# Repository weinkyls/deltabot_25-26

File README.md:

# The Delta Bot

### What is the Delta Bot?
The Delta Bot is an open-source DIY robot AI platform that uses Radxa's single board computer, the [Rock 5B](https://radxa.com/products/rock5/5b/), a simple [camera module](https://www.raspberrypi.com/products/camera-module-v2/), Parallax's [Continuous Rotation Servo Motors](https://www.parallax.com/product/parallax-continuous-rotation-servo-factory-centered/), and the [RPLIDAR A1](https://www.slamtec.com/en/lidar/a1), a LIDAR camera by Slamtec.

### Purpose & Vision

### What can it do?

- 360 Degree 2D LiDAR Scans
- Precise Servo Movement 
- 1080p Video Capture
- Can be configured for Line Following, SLAM, Obstacle Detection, and more!

### Additional Mechanical Parts
Additional Mechanical Parts were designed in CAD and can be accessed [here](additional_files/deltabot.f3z).
These were used to secure the external components onto the Single PCB Chassis:

## Credits
- Saleh AlMulla - 2721704A@student.gla.ac.uk
- Bernd Porr -  bernd.porr@glasgow.ac.uk

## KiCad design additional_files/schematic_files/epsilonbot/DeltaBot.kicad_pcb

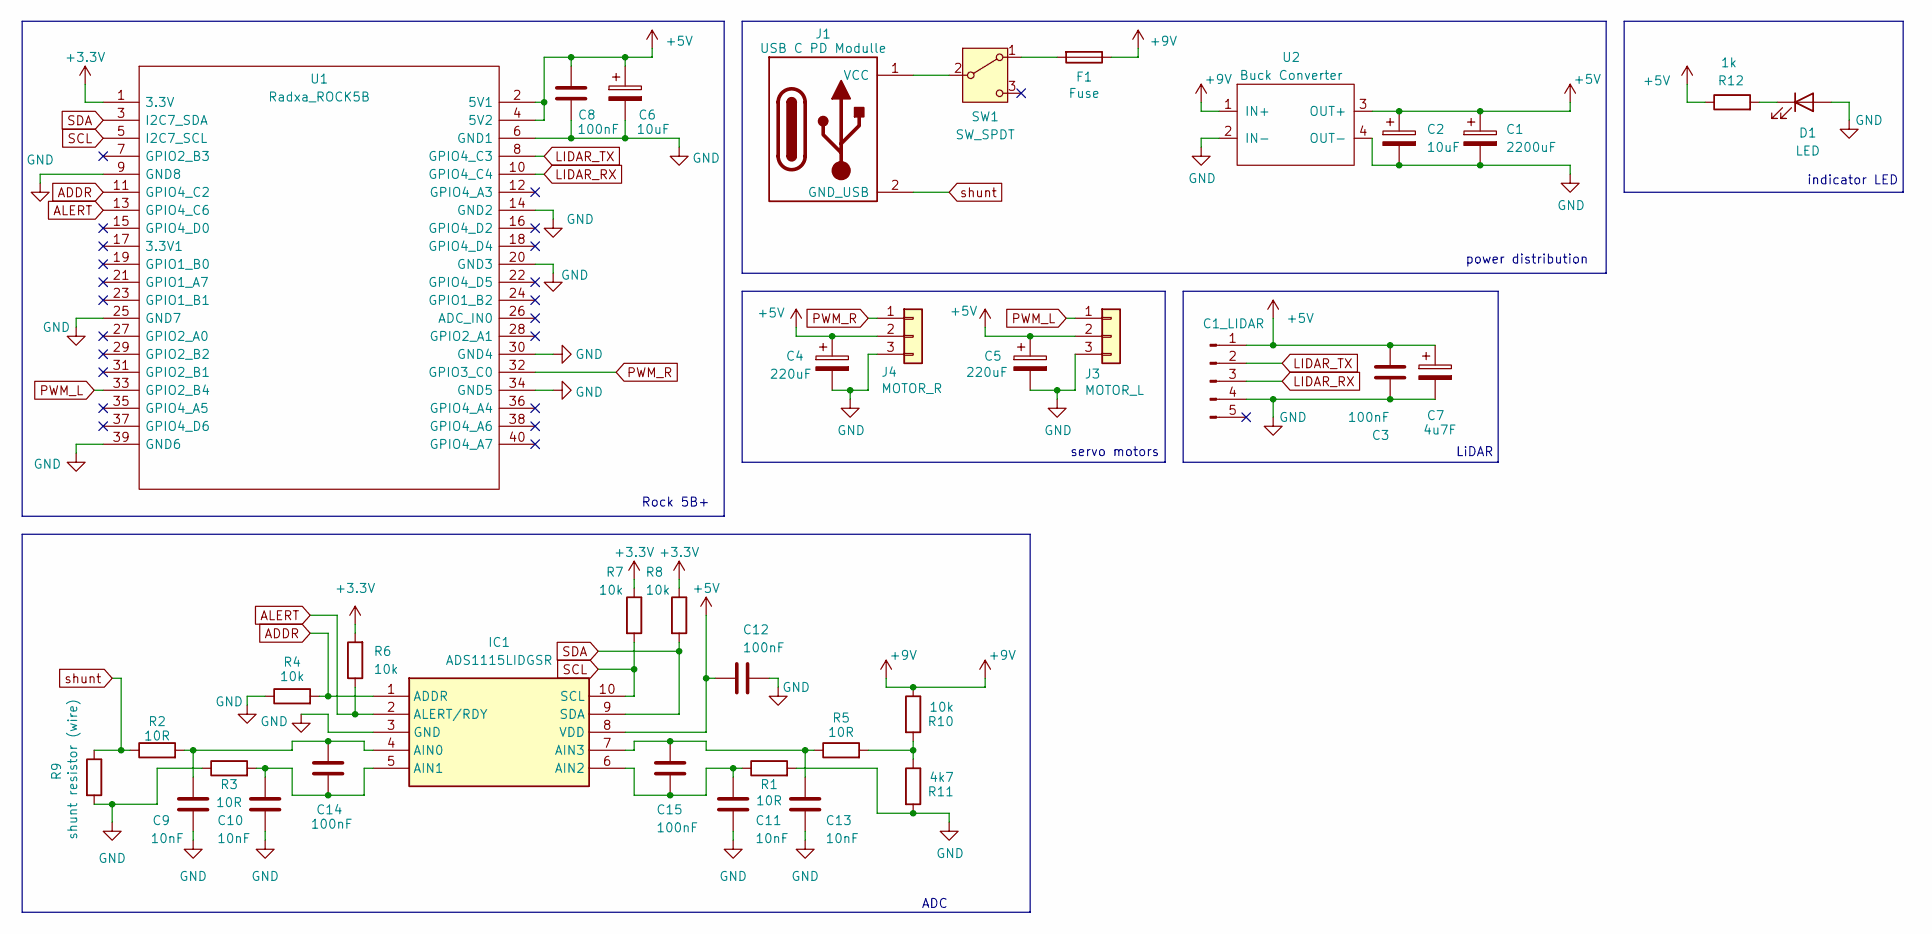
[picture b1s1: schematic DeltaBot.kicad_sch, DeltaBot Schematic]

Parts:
C1: 2200uF; CP_Radial_D16.0mm_P7.50mm
C2: 10uF; CP_Elec_6.3x3
C3, C8, C12, C14, C15: 100nF; C_0805_2012Metric_Pad1.18x1.45mm_HandSolder
C4, C5: 220uF; CP_Elec_10x10
C6: 10uF; CP_Elec_6.3x7.7
C7: 4u7F; CP_Elec_6.3x7.7
C9, C10, C11, C13: 10nF; C_0805_2012Metric_Pad1.18x1.45mm_HandSolder
D1: LED; LED_0805_2012Metric_Pad1.15x1.40mm_HandSolder
F1: Fuse; Fuseholder_Cylinder-5x20mm_Schurter_0031_8201_Horizontal_Op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
IC1: ADS1115LIDGSR; SOP50P490X110-10N; Mouser Part Number 595-ADS1115LIDGSR
J1: USB C PD Modulle; USB_PD
J3: MOTOR_L; PinHeader_1x03_P2.54mm_Vertical
J4: MOTOR_R; PinHeader_1x03_P2.54mm_Vertical
J5: C1_LIDAR; C1 LiDAR
R1, R2, R3, R5: 10R; R_0805_2012Metric_Pad1.20x1.40mm_HandSolder
R4, R6, R7, R8, R10: 10k; R_0805_2012Metric_Pad1.20x1.40mm_HandSolder
R9: shunt resistor (wire); R_0805_2012Metric_Pad1.20x1.40mm_HandSolder
R11: 4k7; R_0805_2012Metric_Pad1.20x1.40mm_HandSolder
R12: 1k; R_0805_2012Metric_Pad1.20x1.40mm_HandSolder
SW1: SW_SPDT; TE_4-1825136-5
U1: Radxa_ROCK5B; ROCK_5B; Manufacturer_Part_Number ROCK5B V1.3
U2: Buck Converter; BUCK_CONV

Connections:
+3.3V: R6.2, R7.1, R8.1, U1.1 (3.3V)
+5V: C1.1, C2.1, C3.1, C4.1, C5.1, C6.1, C7.1, C8.1, C12.2, IC1.8 (VDD), J3.2, J4.2, J5.1 (VCC), R12.1, U1.2 (5V1), U1.4 (5V2), U2.3 (OUT+)
+9V: F1.1, R10.1, U2.1 (IN+)
ADDR: IC1.1 (ADDR), R4.2, U1.11 (GPIO4_C2)
ALERT: IC1.2 (ALERT/RDY), R6.1, U1.13 (GPIO4_C6)
GND: C1.2, C2.2, C3.2, C4.2, C5.2, C6.2, C7.2, C8.2, C9.2, C10.2, C11.2, C12.1, C13.2, D1.2 (A), IC1.3 (GND), J3.3, J4.3, J5.4 (GND), R1.2, R3.1, R4.1, R9.2, R11.2, U1.6 (GND1), U1.9 (GND8), U1.14 (GND2), U1.20 (GND3), U1.25 (GND7), U1.30 (GND4), U1.34 (GND5), U1.39 (GND6), U2.2 (IN-), U2.4 (OUT-)
LIDAR_RX: J5.3 (RX), U1.10 (GPIO4_C4)
LIDAR_TX: J5.2 (TX), U1.8 (GPIO4_C3)
unnamed: D1.1 (K), R12.2
unnamed: C9.1, C14.1, IC1.4 (AIN0), R2.2
unnamed: C10.1, C14.2, IC1.5 (AIN1), R3.2
unnamed: C11.1, C15.2, IC1.6 (AIN2), R1.1
unnamed: C13.1, C15.1, IC1.7 (AIN3), R5.1
unnamed: J1.1 (VCC), SW1.2 (B)
unnamed: R5.2, R10.2, R11.1
unnamed: F1.2, SW1.1 (A)
PWM_L: J3.1, U1.33 (GPIO2_B4)
PWM_R: J4.1, U1.32 (GPIO3_C0)
SCL: IC1.10 (SCL), R7.2, U1.5 (I2C7_SCL)
SDA: IC1.9 (SDA), R8.2, U1.3 (I2C7_SDA)
shunt: J1.2 (GND_USB), R2.1, R9.1

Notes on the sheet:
ADC
servo motors
Rock 5B+
LiDAR
indicator LED
power distribution

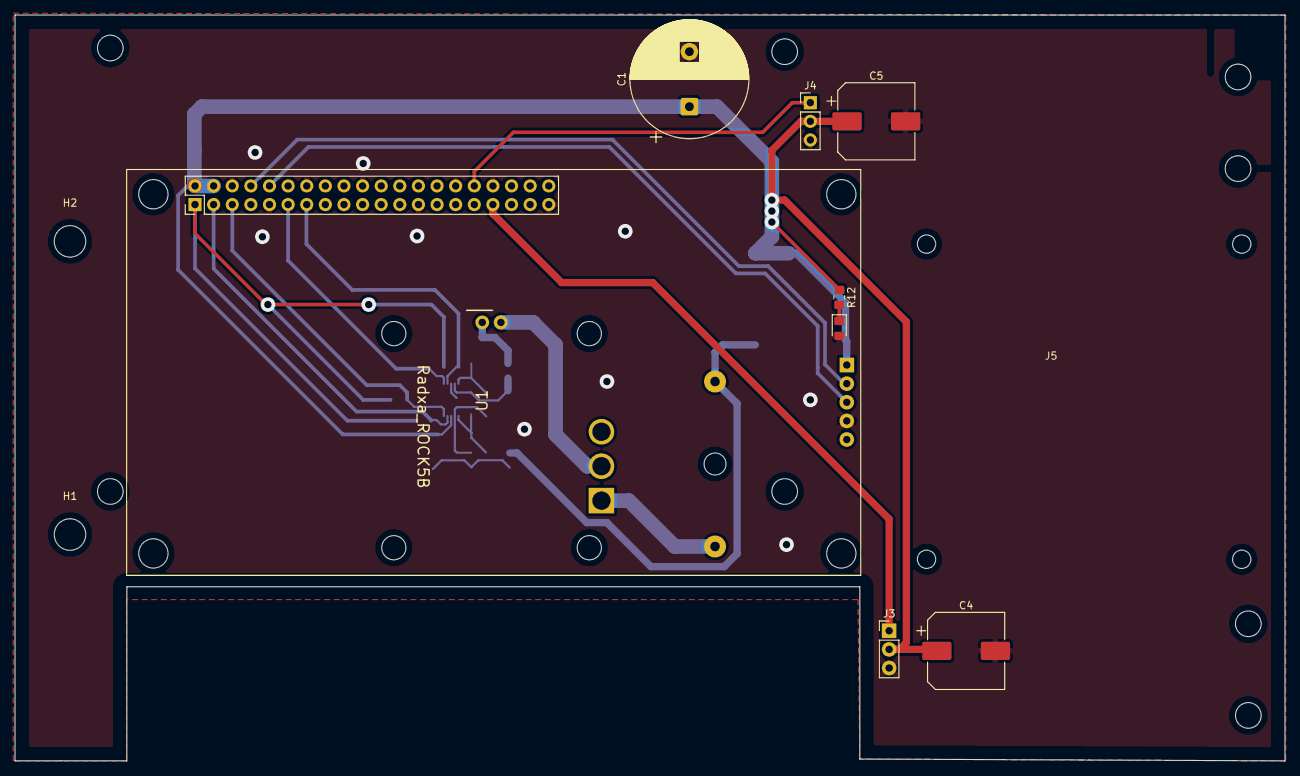
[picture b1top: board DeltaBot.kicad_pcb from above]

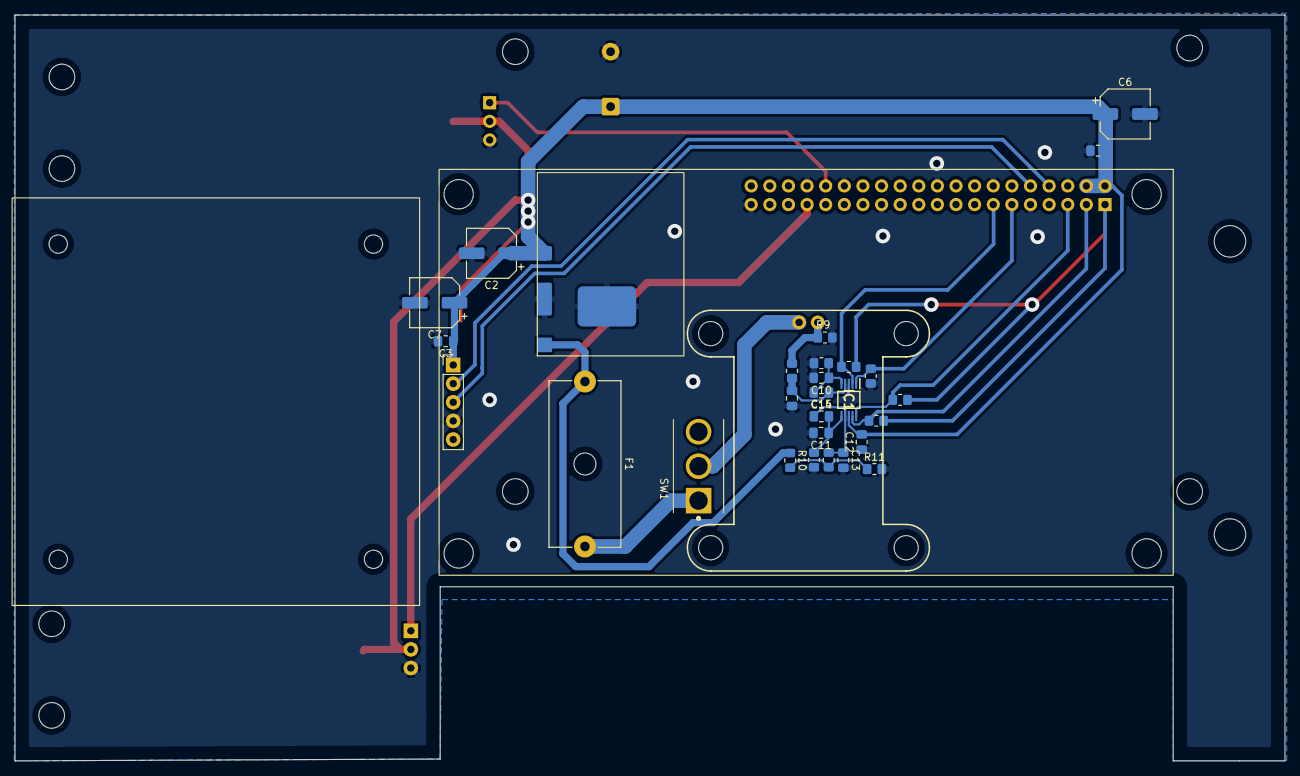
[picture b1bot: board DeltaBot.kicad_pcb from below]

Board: 2 copper layers, 173.2 x 101.8 mm, 39 parts (29 on the bottom side), 21 nets.

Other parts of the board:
H1, H2: MountingHole; MountingHole_4.3mm_M4

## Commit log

2025-11-25 Added YixuanZha's software and made it compile.
2025-11-25 Removed the emacs backup file
2025-11-26 Added instructions how to get PWM and the UART working.
    This is now all done with ARMbian and no longer with the
    vendor image which was just awful. ARMbian has a proper
    config file where one can enable PWM and job done.
2025-11-28 Test Servomotor works!
2025-11-28 Made the test program a bit more usable.
2025-11-30 C1 Lidar works now
2025-11-30 Got rid of the final debug messages.
2025-11-30 Got rid of the AI stuff and the camera code.
2025-11-30 Test bomotion is not working so removed
2025-12-10 More attempts when starting the pwm
2025-12-14 Added a "make install" which installs the header files and library.
2025-12-18 Added wifi setup
2025-12-30 No longer needed as it's now a proper library.
    https://github.com/berndporr/c1lidar
2025-12-31 Replaced the motor control with new classes.
    I've re-written and re-factored the motor drive.
    It now takes speeds from -1 .. +1 as expected
    by the modelchecker.
    There is still one bug in it that when starting the
    motors the 1st time they won't turn. After that
    it works without any problem.
2026-01-01 schematic and modified footprints
2026-01-02 pcb 1st iteration
2026-01-11 file org changes and camera.cpp draft
2026-01-11 changes to camera.h
2026-01-12 drill holes added for battery pack platform and edgecuts for ports
2026-02-04 ADC breakout schematic
2026-02-17 pcb v2
2026-02-17 small changes to pcb
2026-03-06 file re-structuring
2026-03-06 added libraries
2026-03-07 modifying cmakelists.txt (not tested)
2026-03-12 edited repository, it compiles now
    changed cmakelists of metadataprinter in the libcamera library; made edits to the repo's main cmakelists; installed the hdf5 library; editing the syntax of to and other opencv related cmake things; c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
2026-03-13 stereo_camera.cpp v1
    not tested, just getting one camera working for now
2026-03-13 added header file stereo_camera.h
2026-03-13 converted submodules to regular files in /lib
2026-03-18 changes to schematic and pcb
2026-04-02 pcb changes
    rerouted to leave more space for the motors, changed clearance width at the request of the rankine technicians, increased width of traces around the ADC
2026-04-10 added device overlays
2026-04-12 edited cam0 camera overlay, both work together now
2026-04-12 removed build
2026-04-12 removed kicad backups
2026-04-12 updated gitignore
2026-04-13 added opencv camera callback and first draft of stereo camera drivers
2026-04-13 changes to camera_example.cpp
    removed the frame counter and start time loop
2026-04-14 changed camera_example window logic and cmake changes
    was using cv::imshow before, but now switched to using window.h and qtviewer from the opencv-callback library
2026-04-14 convert camera callback from submodule
2026-04-14 hardcode qt platform to linuxfb
2026-04-14 changed video nodes in stereo_camera.cpp and first draft of escape key to escape the camera_example
2026-04-14 changed nodes, changed to self path
2026-04-14 changes to PCB for the ball castor
2026-04-15 isp routing scripts first draft
    one of the csi cables broke so harcode_cam0 is when cam0 is the working camera, and i haven't gotten cam1 to work yet
